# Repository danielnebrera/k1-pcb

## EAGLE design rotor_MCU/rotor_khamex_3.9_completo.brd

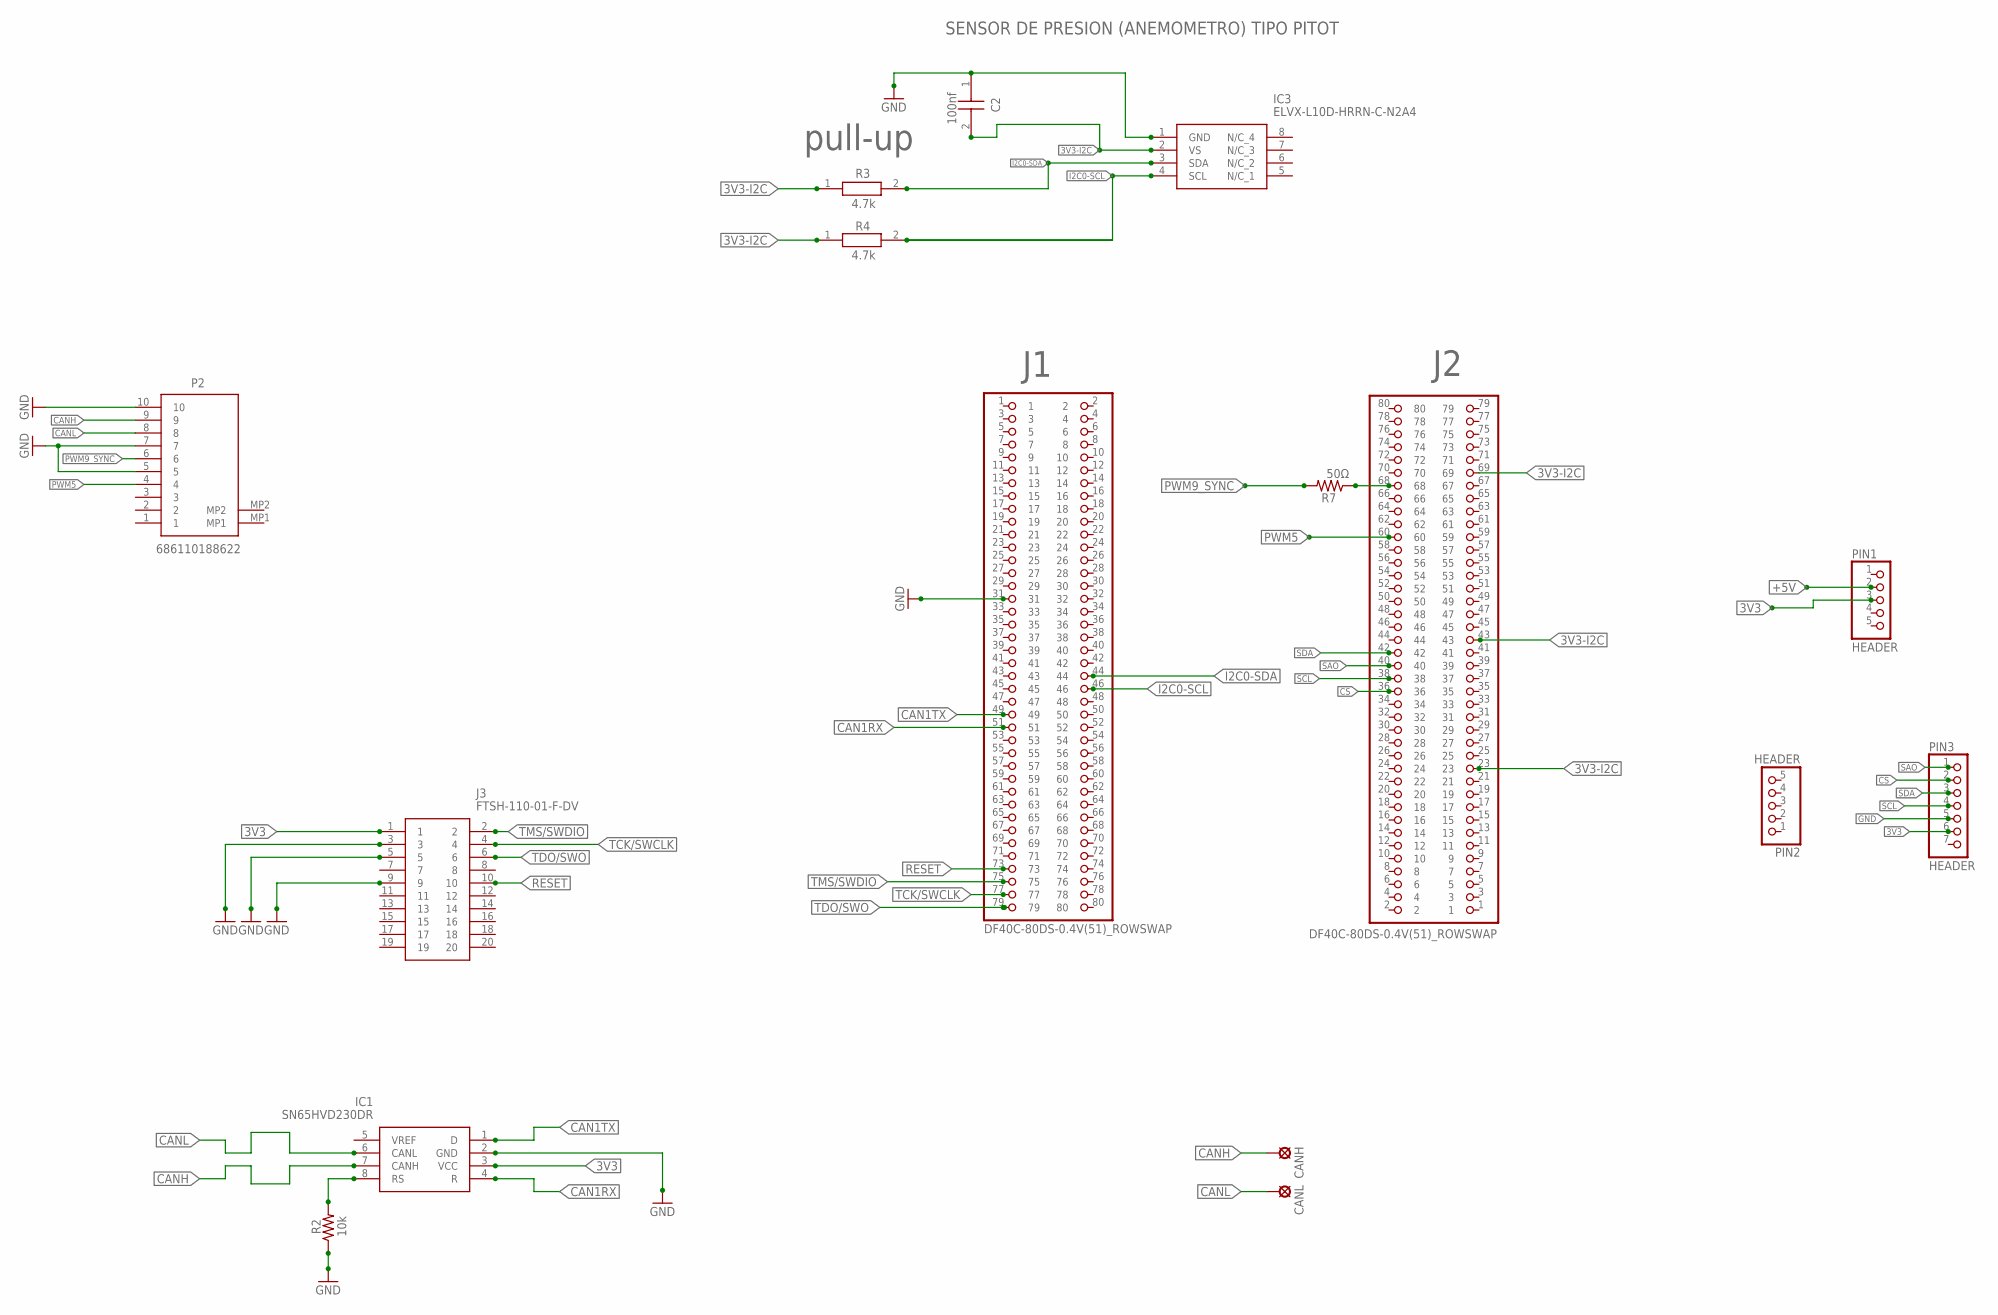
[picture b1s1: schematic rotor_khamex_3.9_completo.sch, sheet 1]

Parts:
C2: 100nf; CAPC2012X145N
CANH: LSP11
CANL: LSP11
IC1: SN65HVD230DR; SOT127P600X175-8N
IC3: ELVX-L10D-HRRN-C-N2A4; ELVXL10DHRRNCN2A4
J1, J2: DF40C-80DS-0.4V(51)_ROWSWAP; HRS_DF40C-80DS-0.4V(51)_ROWSWAP
J3: FTSH-110-01-F-DV; FTSH-110-XX-YYY-DV
P2: 686110188622
PIN1, PIN2: HEADER; 1X05
PIN3: HEADER; 1X07
R2: 10k; M0805
R3, R4: 4.7k; RESC2012X50N
R7: 50Ω; M0805

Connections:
3V3: IC1.3 (VCC), J3.1, PIN1.3, PIN3.6
3V3-I2C: C2.2, IC3.2 (VS), J2.23, J2.43, J2.69, R3.1, R4.1
+5V: PIN1.2; also elsewhere on the board
CAN1RX: IC1.4 (R), J1.51
CAN1TX: IC1.1 (D), J1.49
CANH: CANH.MP, IC1.7 (CANH), P2.9
CANL: CANL.MP, IC1.6 (CANL), P2.8
CS: J2.36, PIN3.2
GND: C2.1, IC1.2 (GND), IC3.1 (GND), J1.31, J3.3, J3.5, J3.9, P2.5, P2.7, P2.10, PIN3.5, R2.1; also elsewhere on the board
I2C0-SCL: IC3.4 (SCL), J1.46, R4.2
I2C0-SDA: IC3.3 (SDA), J1.44, R3.2
unnamed: IC1.8 (RS), R2.2
PWM5: J2.60, P2.4
PWM9_SYNC: J2.68, P2.6, R7.1, R7.2
RESET: J1.73, J3.10
SAO: J2.40, PIN3.1
SCL: J2.38, PIN3.4
SDA: J2.42, PIN3.3
TCK/SWCLK: J1.77, J3.4
TDO/SWO: J1.79, J3.6
TMS/SWDIO: J1.75, J3.2

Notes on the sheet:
SENSOR DE PRESION (ANEMOMETRO) TIPO PITOT
4.7k
pull-up

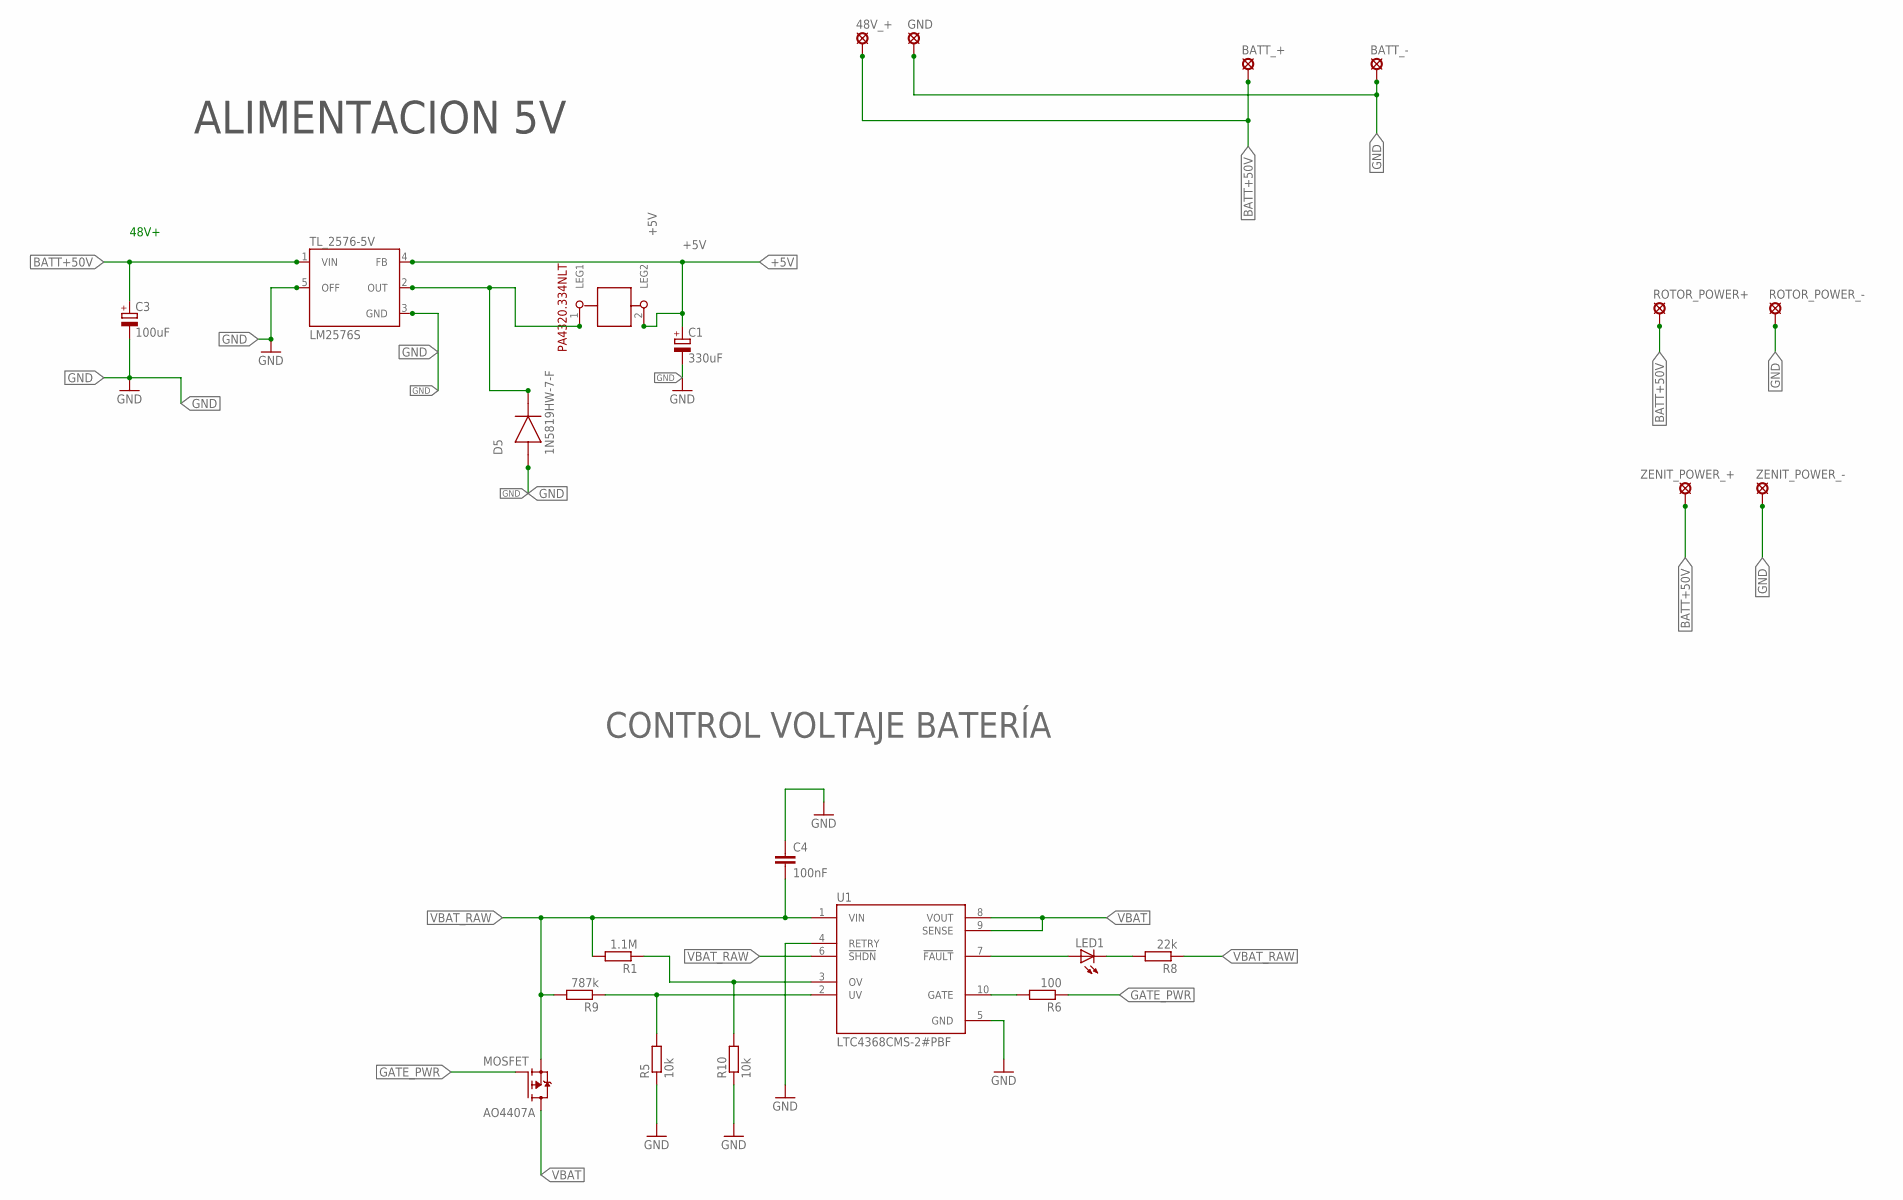
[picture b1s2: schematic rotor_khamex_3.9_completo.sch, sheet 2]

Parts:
48V_+: SE14
BATT_+: SE14
BATT_-: SE14
C1: 330uF; E5-10,5
C3: 100uF; E5-10,5
C4: 100nF; C0805
D5: 1N5819HW-7-F; SOD370155X135
GND: SE14
L: 1212; 1212SMDINDUCTORPACK
LED1: LED; SMARTLED-TTW
MOSFET: AO4407A; SOIC127P600X175-8N
R1: 1.1M; R0805
R5, R10: 10k; R0805
R6: 100; R0805
R8: 22k; R0805
R9: 787k; R0805
ROTOR_POWER+: SE14
ROTOR_POWER_-: SE14
TL_2576-5V: LM2576S; TO263-5
U1: LTC4368CMS-2#PBF; SOP50P490X110-10N
ZENIT_POWER_+: SE14
ZENIT_POWER_-: SE14

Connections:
+5V: C1.+, L.2 (LEG2), TL_2576-5V.4 (FB); also elsewhere on the board
BATT+50V: 48V_+.MP, BATT_+.MP, C3.+, D5.1 (C), L.1 (LEG1), ROTOR_POWER+.MP, TL_2576-5V.1 (VIN), TL_2576-5V.2 (OUT), ZENIT_POWER_+.MP
GATE_PWR: MOSFET.4 (G), R6.1
GND: BATT_-.MP, C1.-, C3.-, C4.1, D5.2 (A), GND.MP, R5.1, R10.1, ROTOR_POWER_-.MP, TL_2576-5V.3 (GND), TL_2576-5V.5 (OFF), U1.4 (RETRY), U1.5 (GND), ZENIT_POWER_-.MP; also elsewhere on the board
unnamed: LED1.A@1 (A), U1.7 (!FAULT)
unnamed: R5.2, R9.1, U1.2 (UV)
unnamed: R1.1, R10.2, U1.3 (OV)
unnamed: LED1.C@1 (C), R8.2
unnamed: R6.2, U1.10 (GATE)
VBAT: MOSFET.5 (D), MOSFET.6 (D), MOSFET.7 (D), MOSFET.8 (D), U1.8 (VOUT), U1.9 (SENSE)
VBAT_RAW: C4.2, MOSFET.1 (S), MOSFET.2 (S), MOSFET.3 (S), R1.2, R8.1, R9.2, U1.1 (VIN), U1.6 (!SHDN)

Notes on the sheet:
48V+
ALIMENTACION 5V
CONTROL VOLTAJE BATERÍA

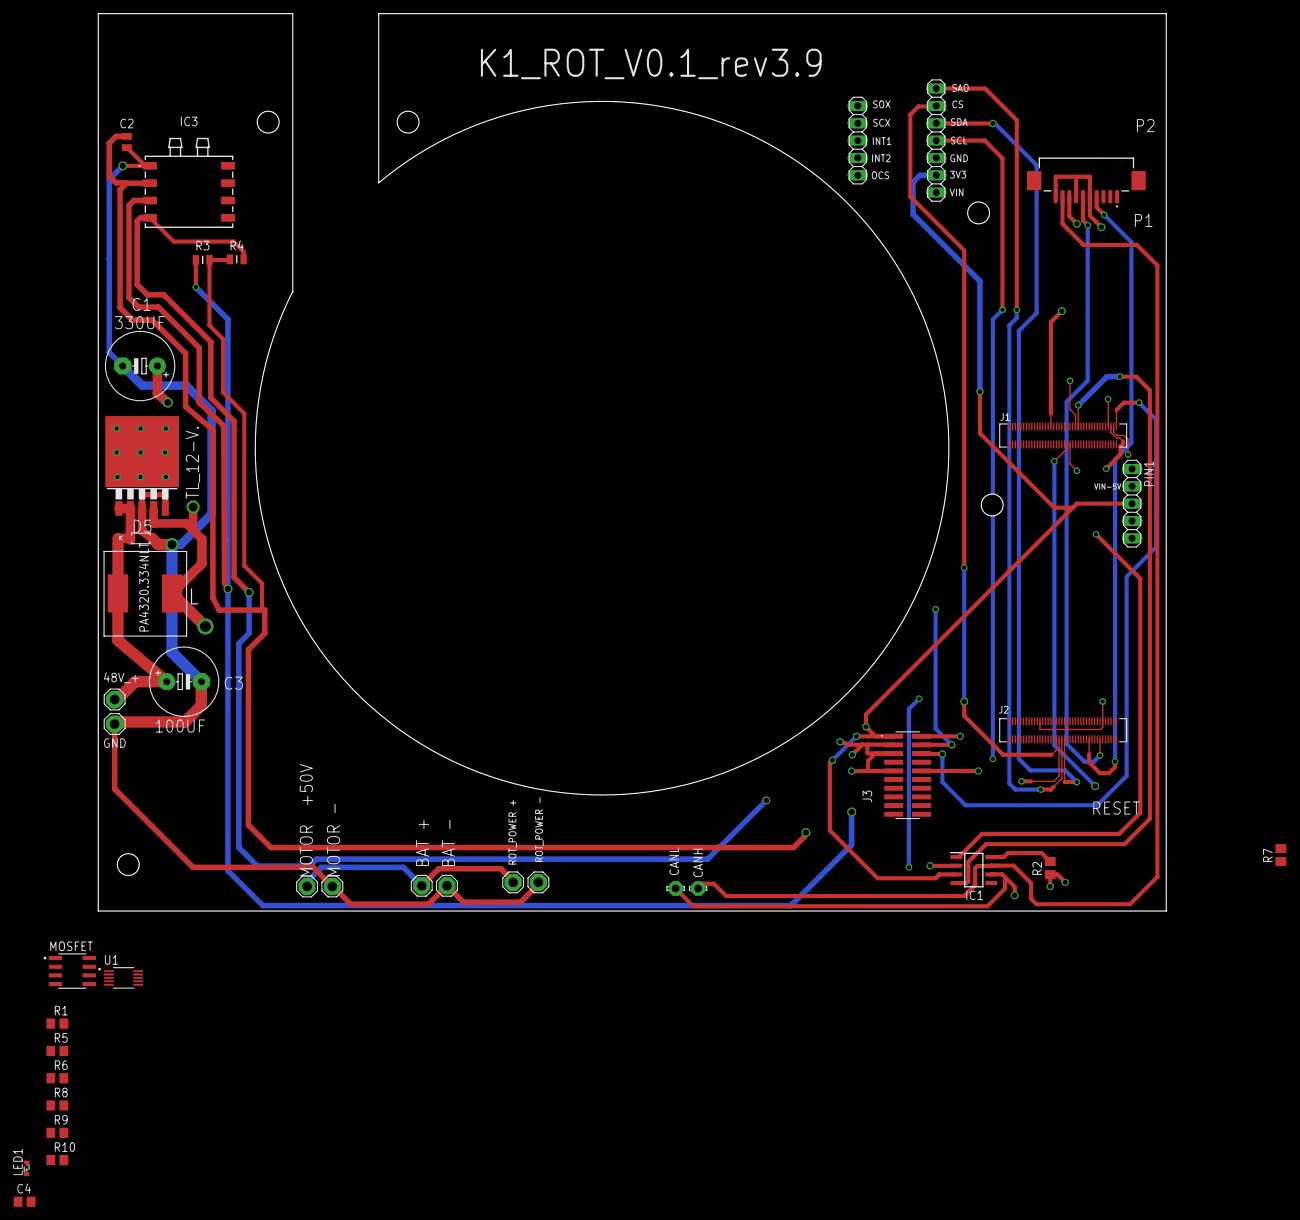
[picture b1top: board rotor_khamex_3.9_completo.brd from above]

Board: 2 copper layers, 156.5 x 131.5 mm, 39 parts (0 on the bottom side), 30 nets.

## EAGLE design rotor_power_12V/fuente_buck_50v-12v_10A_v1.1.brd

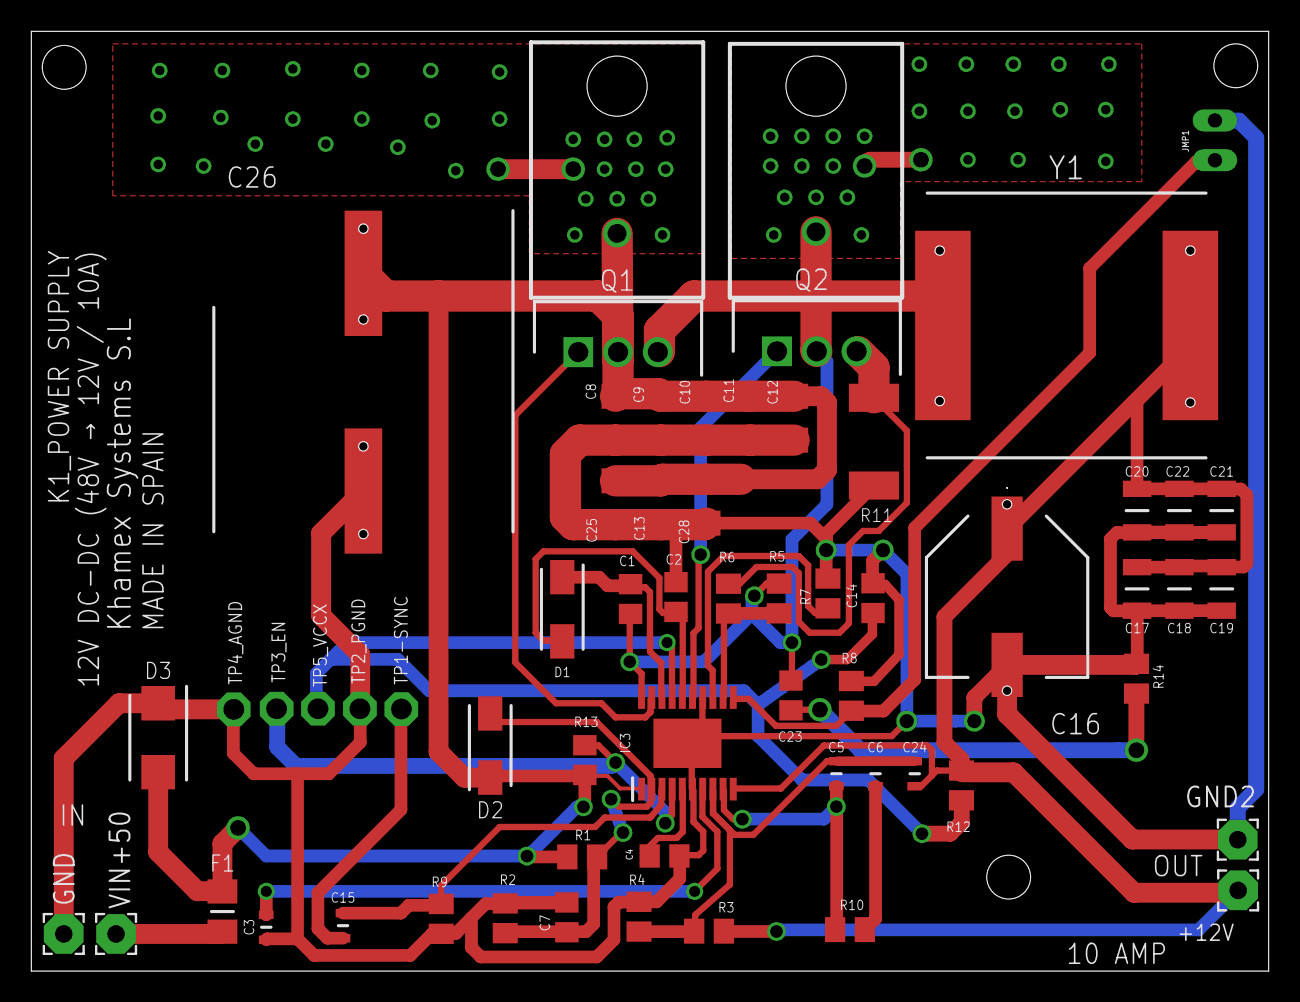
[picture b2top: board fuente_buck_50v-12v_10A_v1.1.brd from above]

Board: 2 copper layers, 79.0 x 60.0 mm, 59 parts (1 on the bottom side), 24 nets.

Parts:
+12V: P3; 2,54/1,1
C1: 0.1uf-x7r _50v; C0805
C2, C14: 1uf_25v; C0805
C3: 0.01uf_50v; CAPC1608X90N
C4: 270PF; C0805
C5, C15: 100pf_50v; CAPC1608X90N
C6: 3300pf_50v; CAPC1608X90N
C7: N/A; C0805
C8, C9, C10, C11: 2.2uf_100v; C1206
C12, C25, C28: 1uf_100v; C1206
C13: 0.1uf_100v; C1206
C16: 330uf 35v; EEE0JA152UAP
C17, C18, C19, C20: 2.2uf_35v; CAPC3216X180N
C21, C22: 1uf_35v; CAPC3216X180N
C23: 220pf_50v; C0805
C24: 47pf_50v; CAPC1608X90N
C26: 330uf_100v; CAPAE1910X1750N
D1, D2: SS16-E3_61T; DIOM5127X229N
D3: SMBJ58A; DIOM5436X261N
F1: 8amp_slow blow; FUSC3216X123N
GND: P2; 2,54/1,1
GND2: P4; 2,54/1,1
IC3: LM5116; SOP65P640X110-21N
JMP1: JP1
Q1, Q2: CSD19506KCS; TO254P470X1016X1611-3P
R1: 56k; M0805
R2: 21k; M0805
R3: 10.7 kΩ; M0805
R4: 1.21 kΩ; M0805
R5: 5.1Ω; M0805
R6: 4.7Ω; M0805
R7: 0; M0805
R8: 10k; M0805
R9: 12.4k; M0805
R10: 18K; M0805
R11: 0.0068Ω; R2512
R12: N/A; M0805
R13: 100k; R0805
R14: 10Ω; M0805
TP1-SYNC: TP1; P1-13
TP2_PGND, TP3_EN, TP4_AGND, TP5_VCCX: TPPAD1-13; P1-13
VIN+50: P1; 2,54/1,1
Y1: AMDLA1707S-150MT; INDPM178169X700N

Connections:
10K: C2.1, D1.2, IC3.16
GND: C2.2, C3.2, C4.2, C7.2, C8.2, C9.2, C10.2, C11.2, C12.2, C13.2, C14.1, C16.2, C17.1, C18.1, C19.1, C20.1, C21.1, C22.1, C25.2, C26.2, C28.2, D3.1, GND.1, GND2.1, IC3.6, IC3.14, IC3.21, JMP1.1, R2.1, R4.1, R7.2, R8.2, R9.1, R11.1, R14.1, TP2_PGND.TP, TP4_AGND.TP
unnamed: C5.1, C6.1, C24.1, IC3.8, R3.2, R4.2
unnamed: F1.1, VIN+50.1
unnamed: C23.2, R14.2
unnamed: C7.1, D2.2, IC3.2, R1.1, R2.2
unnamed: C15.1, IC3.3, R9.2
unnamed: C15.2, TP1-SYNC.TP
unnamed: C4.1, IC3.5
unnamed: C3.1, IC3.7
unnamed: C14.2, IC3.17, R12.1, TP5_VCCX.TP
unnamed: C5.2, IC3.9, R10.2
unnamed: IC3.19, Q1.1
unnamed: C6.2, R10.1
unnamed: +12V.1, C16.1, C17.2, C18.2, C19.2, C20.2, C21.2, C22.2, C24.2, IC3.10, R3.1, R12.2, Y1.2
unnamed: IC3.4, R13.1, TP3_EN.TP
unnamed: IC3.15, Q2.1
unnamed: C1.2, D1.1, IC3.18
unnamed: IC3.13, R7.1
unnamed: Q2.3, R6.2, R11.2
unnamed: IC3.11, JMP1.2, R8.1
unnamed: IC3.12, R5.1, R6.1
SW: C1.1, C23.1, IC3.20, Q1.3, Q2.2, R5.2, Y1.1
VIN: C8.1, C9.1, C10.1, C11.1, C12.1, C13.1, C25.1, C26.1, C28.1, D2.1, D3.2, F1.2, IC3.1, Q1.2, R1.2, R13.2
